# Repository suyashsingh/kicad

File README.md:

# Learning KiCad
Following along with official KiCad tutorial.

## 1. Schematic

## 2. Board Layout

## 3. 3D-Model

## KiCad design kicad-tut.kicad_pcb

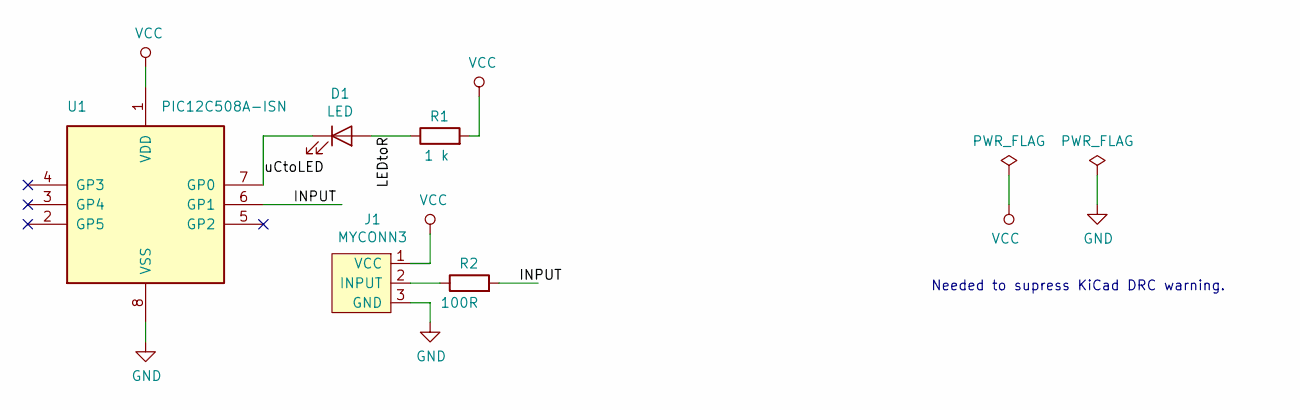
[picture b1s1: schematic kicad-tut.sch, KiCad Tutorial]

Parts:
D1: LED; LED_D5.0mm
J1: MYCONN3; Banana_Jack_3Pin
R1: 1 k; R_Axial_DIN0204_L3.6mm_D1.6mm_P7.62mm_Horizontal
R2: 100R; R_Axial_DIN0204_L3.6mm_D1.6mm_P7.62mm_Horizontal
U1: PIC12C508A-ISN; DIP-8_W7.62mm

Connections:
/INPUT: R2.2, U1.6 (GP1)
/LEDtoR: D1.2 (A), R1.1
/uCtoLED: D1.1 (K), U1.7 (GP0)
GND: J1.3 (GND), U1.8 (VSS)
unnamed: J1.2 (INPUT), R2.1
VCC: J1.1 (VCC), R1.2, U1.1 (VDD)

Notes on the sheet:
Needed to supress KiCad DRC warning.

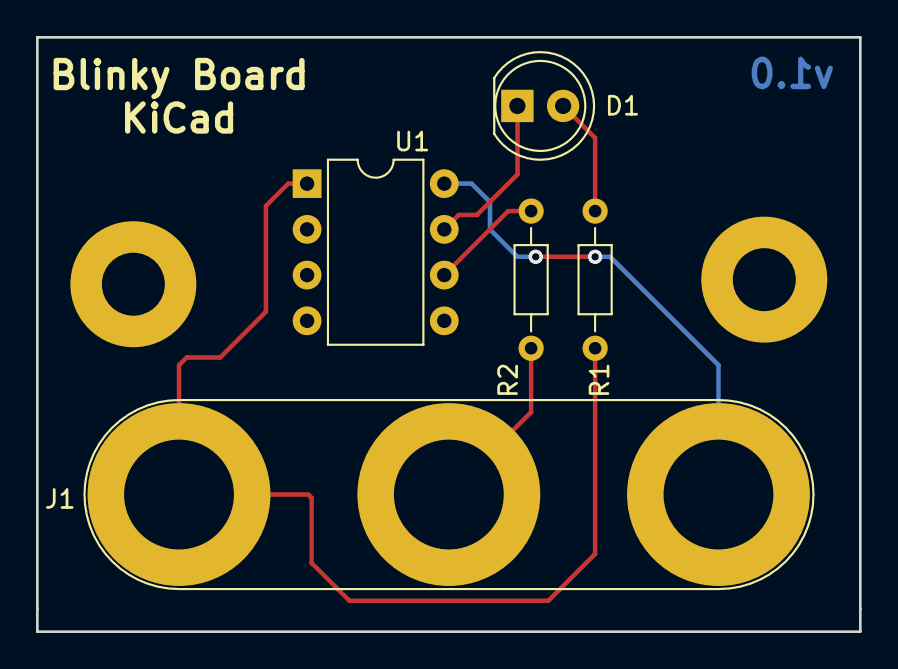
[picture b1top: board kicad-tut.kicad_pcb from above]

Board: 2 copper layers, 45.7 x 33.0 mm, 5 parts (0 on the bottom side), 6 nets.

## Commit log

2019-09-11 Added inital project files.
2019-09-11 added sym-lib-table(auto generated): fixed broken path to custom library.
2019-09-11 completed board routing
2019-09-11 Made final changes to the board design and added screenshots of the board.
2019-09-11 updated readme with pictures of the board
2019-09-12 reexported gerbers(excluded values from being exported), fixed missing board name in the front silk screen & updated readme
2019-09-12 commiting missed out files in the last commit
